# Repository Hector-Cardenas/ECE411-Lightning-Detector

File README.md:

Github Repo for the lightning detector, AKA the THUNDER BUDDY.

All source code downloads require installation of the pico-sdk, instructions can be found at https://www.raspberrypi.com/news/get-started-with-raspberry-pi-pico-series-and-vs-code/ \
Building and compiling was done on a linux machine to produce a .uf2 file to drag and drop into the pico w when in BOOTSEL mode. This is the recommended way to build the project\
For Linux terminal use:\
Clone this repo\
cd ECE411-THUNDER-BUDDIES/software/src\
mkdir build\
cd build\
cmake ..\
make ThunderBuddy\
Drag and drop the .uf2 file into the pico w 

Re-making the project just requires a Make clean and a Make Thunderbuddy
If any of the debug options want to be added or removed one must remove the CMakeCache.txt file in /build before using a new cmake command

CMake options (set the option to =1 to select the argument):\
-DPRINT will print messages to stdout\
-DFLASH will flash the onboard LED when transmitting\
-DFORCE will force an lightning detected condition always\
-DPRINTFLASH combines flash and print\
-DPRINTFORCE combines force and print\
-DDEBUG enables all debug modes\

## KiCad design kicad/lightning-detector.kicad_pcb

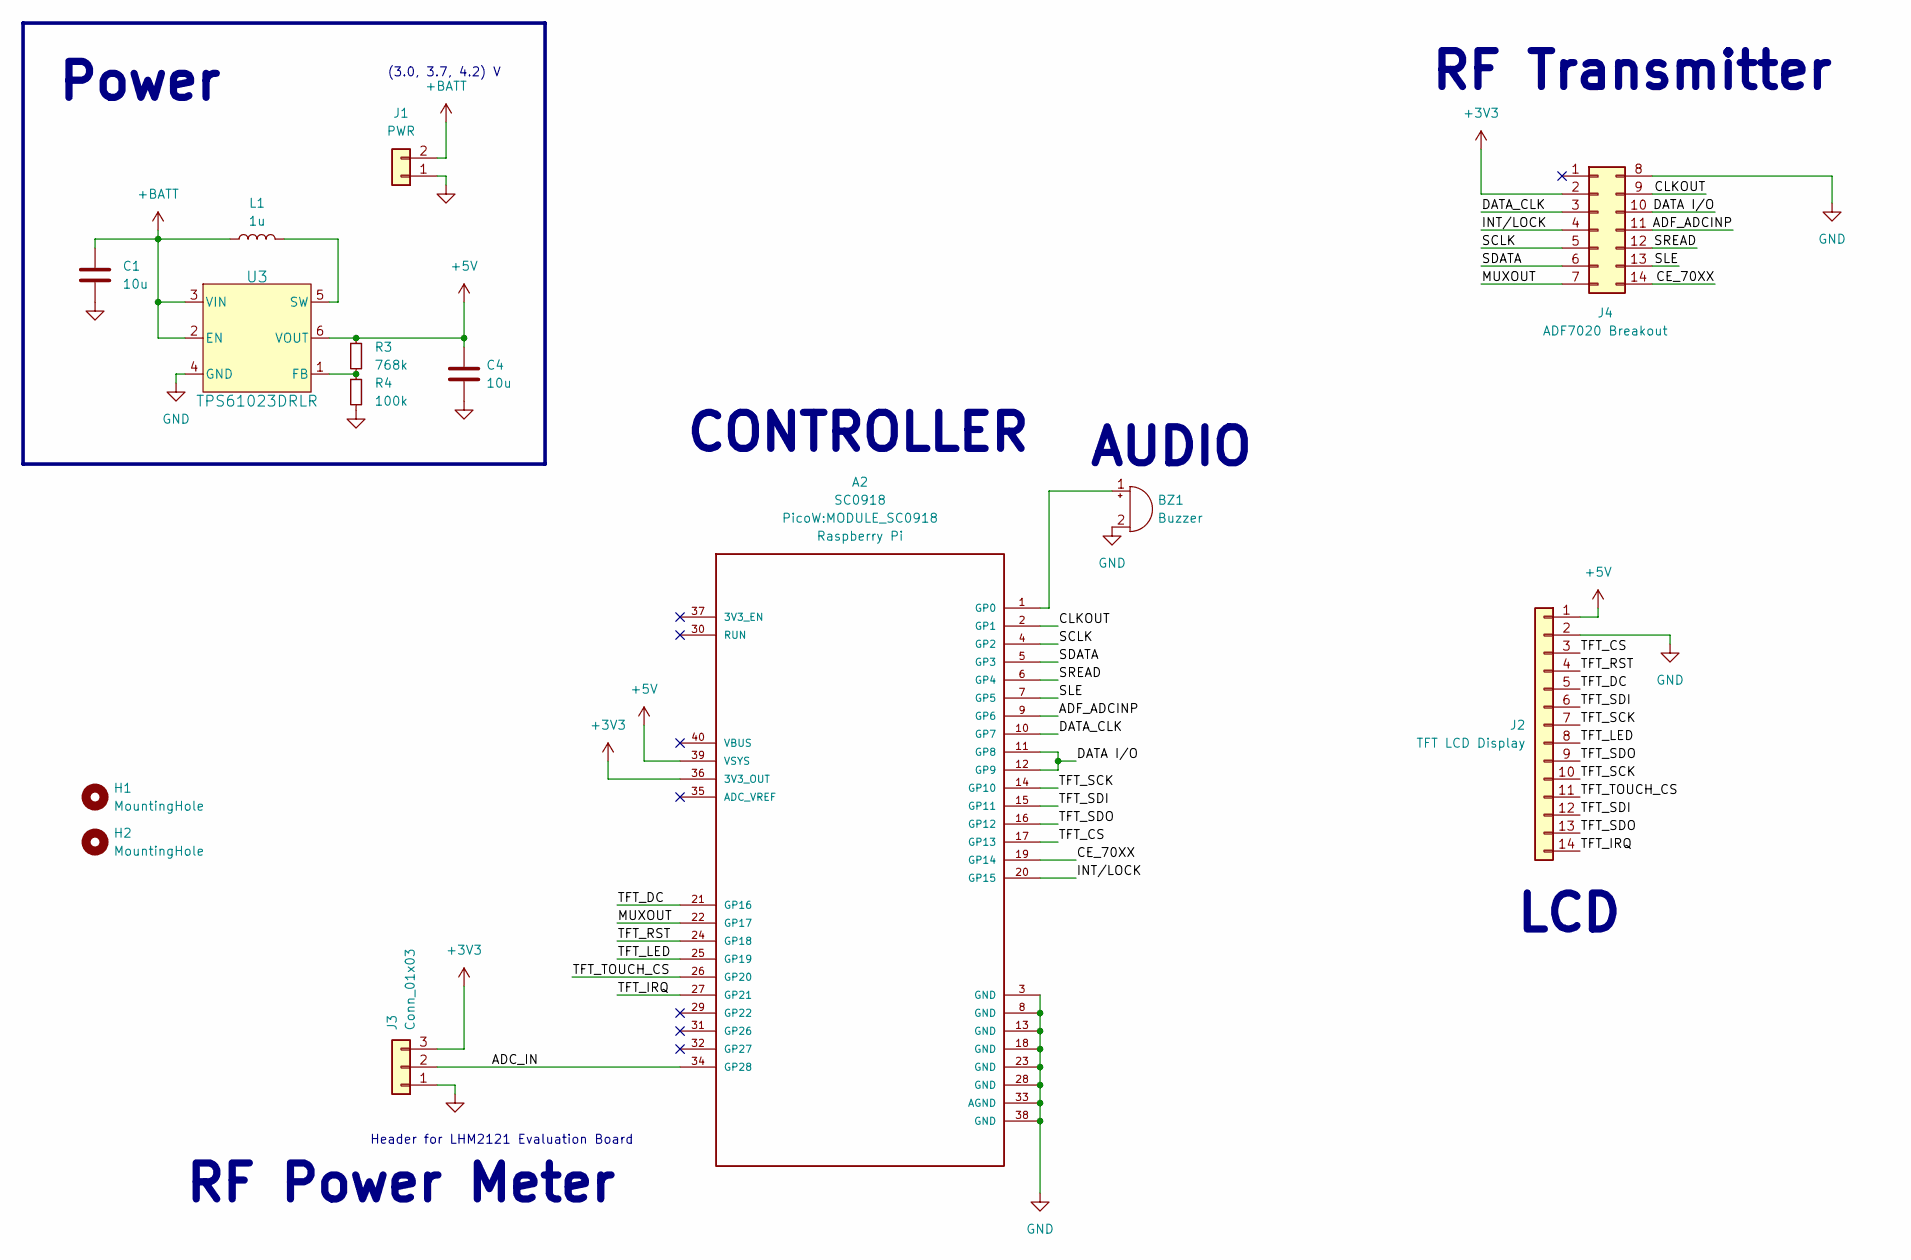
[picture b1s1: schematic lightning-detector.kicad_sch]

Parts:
A2: SC0918; MODULE_SC0918; PARTREV 1.6
BZ1: Buzzer; Buzzer_12x9.5RM7.6
C1, C4: 10u; C_0603_1608Metric
H1, H2: MountingHole; MountingHole_2.7mm_M2.5
J1: PWR; PinHeader_1x02_P2.54mm_Vertical
J2: TFT LCD Display; PinHeader_1x14_P2.54mm_Vertical
J3: Conn_01x03; PinHeader_1x03_P2.54mm_Vertical
J4: ADF7020 Breakout; IDC-Header_2x07_P2.54mm_Vertical
L1: 1u; L_1008_2520Metric
R3: 768k; R_0603_1608Metric
R4: 100k; R_0603_1608Metric
U3: TPS61023DRLR; SOT563-ORI

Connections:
+3V3: A2.36 (3V3_OUT), J3.3, J4.2
+5V: A2.39 (VSYS), C4.1, J2.1, R3.1, U3.6 (VOUT)
+BATT: C1.1, J1.2, L1.1, U3.2 (EN), U3.3 (VIN)
/ADC_IN: A2.34 (GP28), J3.2
/ADF_ADCINP: A2.9 (GP6), J4.11
/CE_70XX: A2.19 (GP14), J4.14
/CLKOUT: A2.2 (GP1), J4.9
/DATA I/O: A2.11 (GP8), A2.12 (GP9), J4.10
/DATA_CLK: A2.10 (GP7), J4.3
/INT/LOCK: A2.20 (GP15), J4.4
/MUXOUT: A2.22 (GP17), J4.7
/SCLK: A2.4 (GP2), J4.5
/SDATA: A2.5 (GP3), J4.6
/SLE: A2.7 (GP5), J4.13
/SREAD: A2.6 (GP4), J4.12
/TFT_CS: A2.17 (GP13), J2.3
/TFT_DC: A2.21 (GP16), J2.5
/TFT_IRQ: A2.27 (GP21), J2.14
/TFT_LED: A2.25 (GP19), J2.8
/TFT_RST: A2.24 (GP18), J2.4
/TFT_SCK: A2.14 (GP10), J2.7, J2.10
/TFT_SDI: A2.15 (GP11), J2.6, J2.12
/TFT_SDO: A2.16 (GP12), J2.9, J2.13
/TFT_TOUCH_CS: A2.26 (GP20), J2.11
GND: A2.3 (GND), A2.8 (GND), A2.13 (GND), A2.18 (GND), A2.23 (GND), A2.28 (GND), A2.33 (AGND), A2.38 (GND), BZ1.2 (-), C1.2, C4.2, J1.1, J2.2, J3.1, J4.8, R4.2, U3.4 (GND)
unnamed: A2.1 (GP0), BZ1.1 (+)
unnamed: R3.2, R4.1, U3.1 (FB)
unnamed: L1.2, U3.5 (SW)

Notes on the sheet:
LCD
RF Power Meter
AUDIO
Power
CONTROLLER
(3.0, 3.7, 4.2) V
Header for LHM2121 Evaluation Board
RF Transmitter

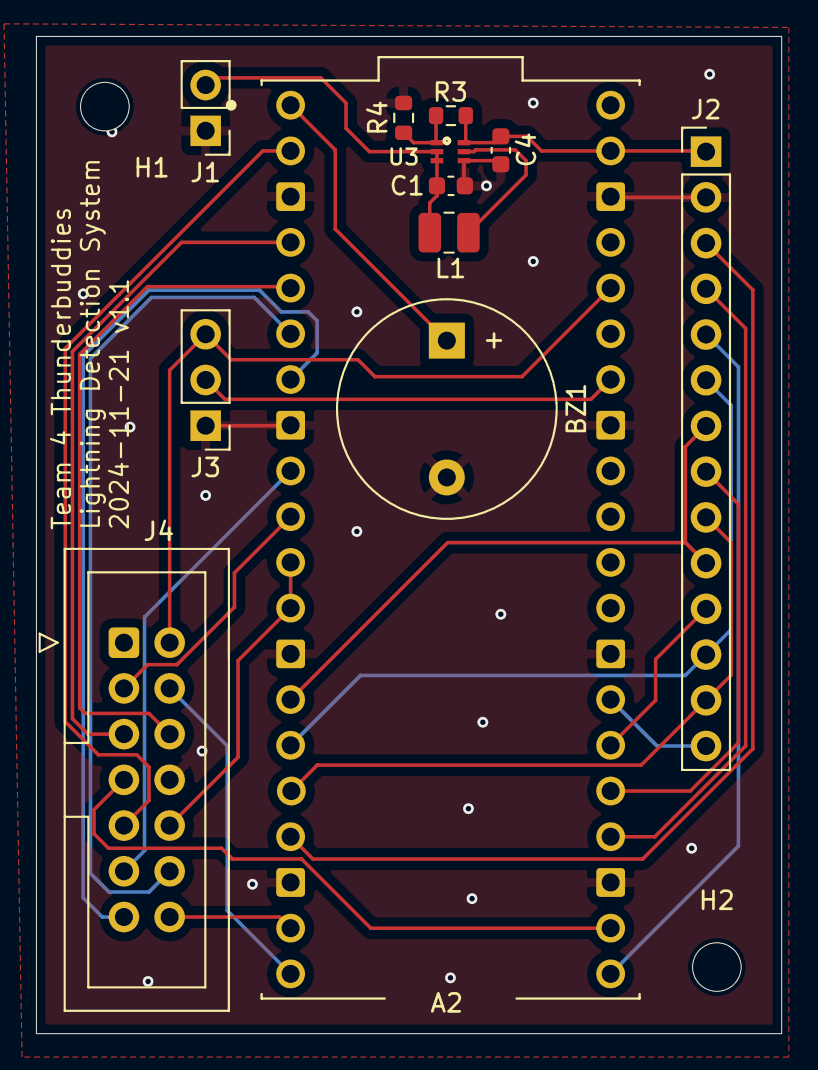
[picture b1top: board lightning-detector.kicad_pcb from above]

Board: 2 copper layers, 41.4 x 55.4 mm, 14 parts (0 on the bottom side), 28 nets.

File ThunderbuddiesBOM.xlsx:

Bill Of Materials for: Team 4 Thunderbuddies
Last modified: 2024-11-14
PCB version: v0.1a
BOM revision: v0.1a |  | P/NP | = Place/Not Place (components marked NP are not stuffed on the board)
Cnt | Part References | P/NP | Mfg | Mfg PN | Description | Generic | Dist | Dist Part Number | Cost Ea. | Cost Total
1.0 | A2 | P | Raspberry Pi | SC0918 | Pico W RP2040-based MCU Board | N | Digikey | 2648-SC0918CT-ND | 6.0 | 6
1.0 | BZ1 | P | Soberton | GT-0903A | 3V Buzzer | Y | Digikey | 433-1032-ND | 0.97 | 0.97
2.0 | C1, C4 | P | N/A | N/A | 10uF 0603 SMD Ceramic Capacitor | Y | N/A | N/A | 0.25 | 0.5
1.0 | J1 | P | N/A | N/A | 2.54mm Header, 2 Pins | Y | N/A | N/A | 0.01 | 0.01
1.0 | J3 | P | N/A | N/A | 2.54mm Header, 3 Pins | Y | N/A | N/A | 0.01 | 0.01
1.0 | J4 | P | N/A | N/A | 2.54mm Header, 14 Pins, IDC | Y | N/A | N/A | 0.01 | 0.01
1.0 | L1 | P | N/A | N/A | 1uH Inductor, 1A current carrying capacity | Y | N/A | N/A | 0.25 | 0.25
1.0 | R3 | P | N/A | N/A | 768k, 1% tolerance | Y | N/A | N/A | 0.1 | 0.1
1.0 | R4 | P | N/A | N/A | 100k, 1% tolerance | Y | N/A | N/A | 0.1 | 0.1
1.0 | U3 | P | Texas Instruments | TPS61023DRLR | Boost Switching Regulator IC, Adjustable Output | N | Digikey | 296-TPS61023DRLRCT-ND | 0.89 | 0.89
1.0 | N/A | P | Analog Devices | EVAL-ADF7020-1DBZ8 | RF Transciever, 128MHz - 142MHz Evaluation Board | N | Digikey | 505-EVAL-ADF7020-1DBZ8-ND | 117.45 | 117.45
1.0 | N/A | P | Texas Instruments | LMH2121TMEVAL/NOPB | RF Power Detector 100MHz - 3GHz, Evaluation Board | N | Digikey | 296-45776-ND | 118.8 | 118.8
 |  |  |  |  |  |  |  |  |  | 0
 |  |  |  |  |  |  |  |  | TOTAL: | 245.09
VERSION INFO
Rev | Date | Notes
0.1a | 45610.0 | Initial BOM.

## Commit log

2024-10-24 Adding PDS to repository
2024-10-24 Minor formatting corrections to PDS
    Caught minor inconsistencies in heading formatting (use of colons, bullet list); this upload is the updated version
2024-10-24 Delete Team_4_Product_Design_Specification.pdf
    Deleting old PDS with formatting inconsistencies
2024-10-24 prelim schematic
2024-10-28 Create Meeting Notes
    Creating meeting notes. Added notes for 28OCT2024
2024-10-28 Update Meeting Notes
    Edited notes from 28OCT2024
2024-11-02 Update Meeting Notes
    Added meeting notes for 01NOV2024
2024-11-03 Adding software directory with blank main.c file in src
2024-11-04 Update Meeting Notes
    Added deliverables for Thursday class time and for Friday huddle
2024-11-05 Update Meeting Notes
    Clarifying when PDS update needs done
2024-11-07 breadboard prototype
2024-11-07 rust test code
2024-11-07 Team schedule
2024-11-07 Updated schematic and created preliminary PCB.
2024-11-09 Meeting notes for 11-8-24
2024-11-12 Create README.md
    Add a short readme
2024-11-12 Update README.md
    Spelling error
2024-11-12 ThunderBuddy interrupt
2024-11-12 Adding CMake
    Adding CMake, merging ThunderBuddies.c offline to prevent rebasing issues.
2024-11-12 Added interrupt to main code
2024-11-14 Adding 3rd party KiCad files to repository
2024-11-14 Added 3rd party files
2024-11-14 Adding 3rd party files
2024-11-14 cleanup structure
2024-11-14 Adding 3rd party files (#4)
    ---------
2024-11-14 Added Functional Decomposition
    Adding Decomp PDF as well as updated PDS with revised block diagrams and brief system description.
2024-11-14 Delete Team 4 PDS.pdf
    Removed old PDS
2024-11-14 wk07 items
2024-11-14 wk07 fix
2024-11-14 add bom
2024-11-18 Update Meeting Notes
    18NOV2024 Meeting Notes
2024-11-20 Create DesignReviewNotes
    Design Review from Chris Kane-Pardy and Caleb Monti
2024-11-20 Update DesignReviewNotes
    Missed one comment about screen
2024-11-20 Repo cleanup; added docs and schematic folders for assignment docs and assignment schematics
2024-11-21 Adding PDF version of design review notes
2024-11-21 Adding PDF versions of schematic and PCB for week 7 assignment
2024-11-21 v1.1, new schematic/pcb
2024-11-21 add schematic and layout pdfs
2024-11-23 SPI initialization and environment for linux build and make
2024-11-23 Removed old files
2024-11-23 Adding sdk import file
2024-11-23 Making config word macros uint32_t type instead of default compile type. SPI functions changed to take uint32_t argument
2024-11-23 Update README.md
    Add instructions for download and compile on linux/UNIX-based terminals.
2024-11-23 Update README.md
    Formatting
2024-11-23 Adding conditional compilation.\Adding 7020 transmit functions
2024-11-23 Clean up comments, add packet transmission for AD7020 transmitter. Fixed compile issues with packet transmission.
2024-11-25 Switched to software interrupt, got LED to flash when over threshold
2024-11-25 Fixed a small issue with an #ifdef
2024-11-25 Added conditional compilation to source code
2024-11-25 Added compile time definitions to cmake to support conditional compilation
2024-11-25 LED flashes when transmit
2024-11-25 Update README.md
    Added CMake options to readme
2024-11-25 Fixed merge conflicts in ThunderBuddy.c
2024-11-26 Added newlines to debug print statements
2024-11-26 add mounting holes
2024-11-26 Added newlines to debug print statements and added an initial sleep to see the transceiver initialization
2024-12-05 add test plan
2024-12-06 Changes including the UART transmission output and buzzer output
